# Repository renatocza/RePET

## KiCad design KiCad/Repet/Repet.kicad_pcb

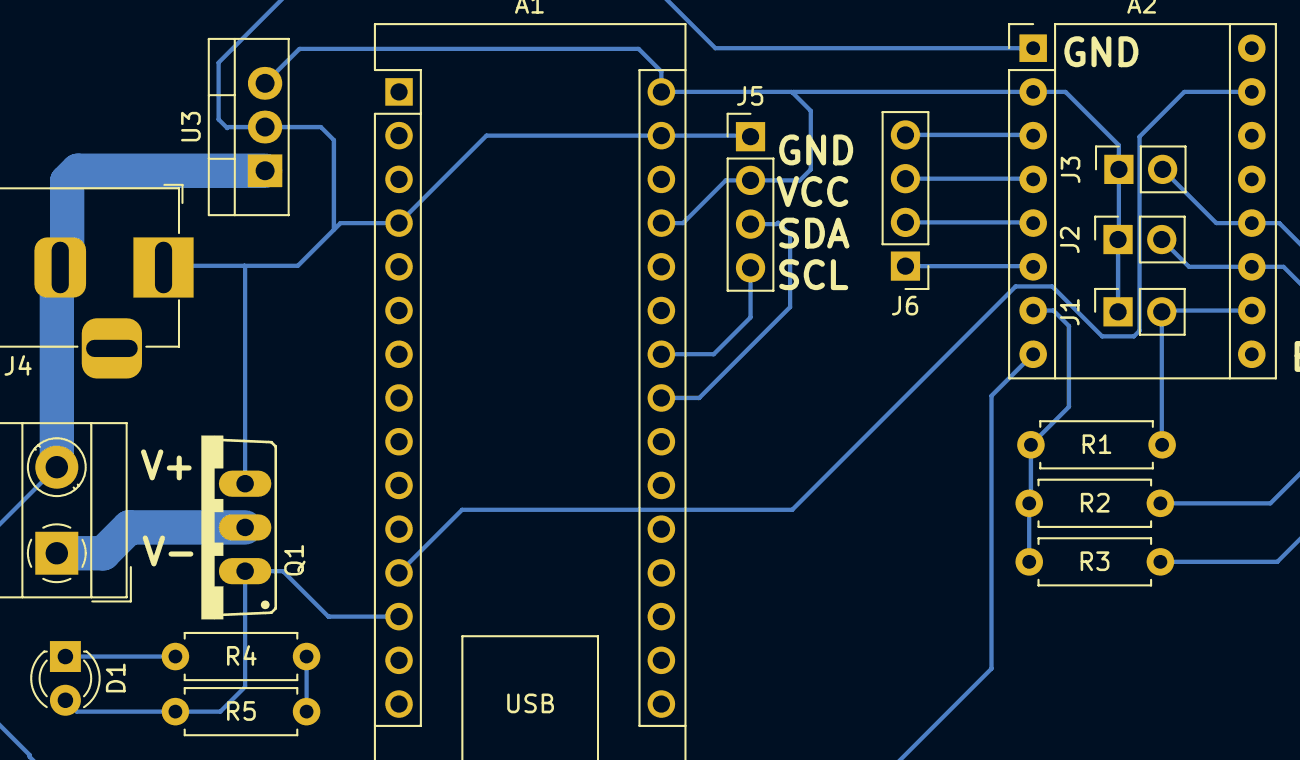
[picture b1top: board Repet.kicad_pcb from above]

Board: 2 copper layers, 17 parts (0 on the bottom side), 16 nets.

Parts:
A1: Arduino_Nano
A2: A4988; Pololu_Breakout-16_15.2x20.3mm
D1: LED; LED_D3.0mm
H1: Screw_Terminal_01x02; TerminalBlock_MetzConnect_Type055_RT01502HDWU_1x02_P5.00mm_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
J1: MS1; PinSocket_1x02_P2.54mm_Vertical
J2: MS2; PinSocket_1x02_P2.54mm_Vertical
J3: MS3; PinSocket_1x02_P2.54mm_Vertical
J4: Barrel_Jack_MountingPin; BarrelJack_Horizontal
J5: LCD; PinHeader_1x04_P2.54mm_Vertical
J6: Stepper_Motor; PinHeader_1x04_P2.54mm_Vertical
Q1: IRF520; TO220BV
R1, R2, R3, R4, R5: 1k; R_Axial_DIN0207_L6.3mm_D2.5mm_P7.62mm_Horizontal
U3: LM7805_TO220; TO-220-3_Vertical

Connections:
GND: A1.4 (GND), A1.29 (GND), A2.1 (GND), A2.7 (GND), J4.1, J5.1, Q1.S, R1.2, R2.2, R3.2, R4.2, R5.2, U3.2 (GND)
unnamed: A1.27 (+5V), A1.30 (VIN), A2.2 (VDD), J1.1, J2.1, J3.1, J5.2, U3.3 (VO)
unnamed: A1.12 (D9), A2.15 (STEP)
unnamed: A1.13 (D10), D1.2 (A), Q1.G, R5.1
unnamed: A1.24 (SCL/A5), J5.4
unnamed: A1.23 (SDA/A4), J5.3
unnamed: A2.4 (1A), J6.3
unnamed: A2.3 (1B), J6.4
unnamed: A2.5 (2A), J6.2
unnamed: A2.6 (2B), J6.1
unnamed: A2.10 (MS1), J1.2, R1.1
unnamed: A2.11 (MS2), J2.2, R2.1
unnamed: A2.12 (MS3), J3.2, R3.1
unnamed: D1.1 (K), R4.1
unnamed: H1.1, Q1.D
VCC: A2.8 (VMOT), H1.2, J4.2, U3.1 (VI)

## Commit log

2023-03-15 no message
